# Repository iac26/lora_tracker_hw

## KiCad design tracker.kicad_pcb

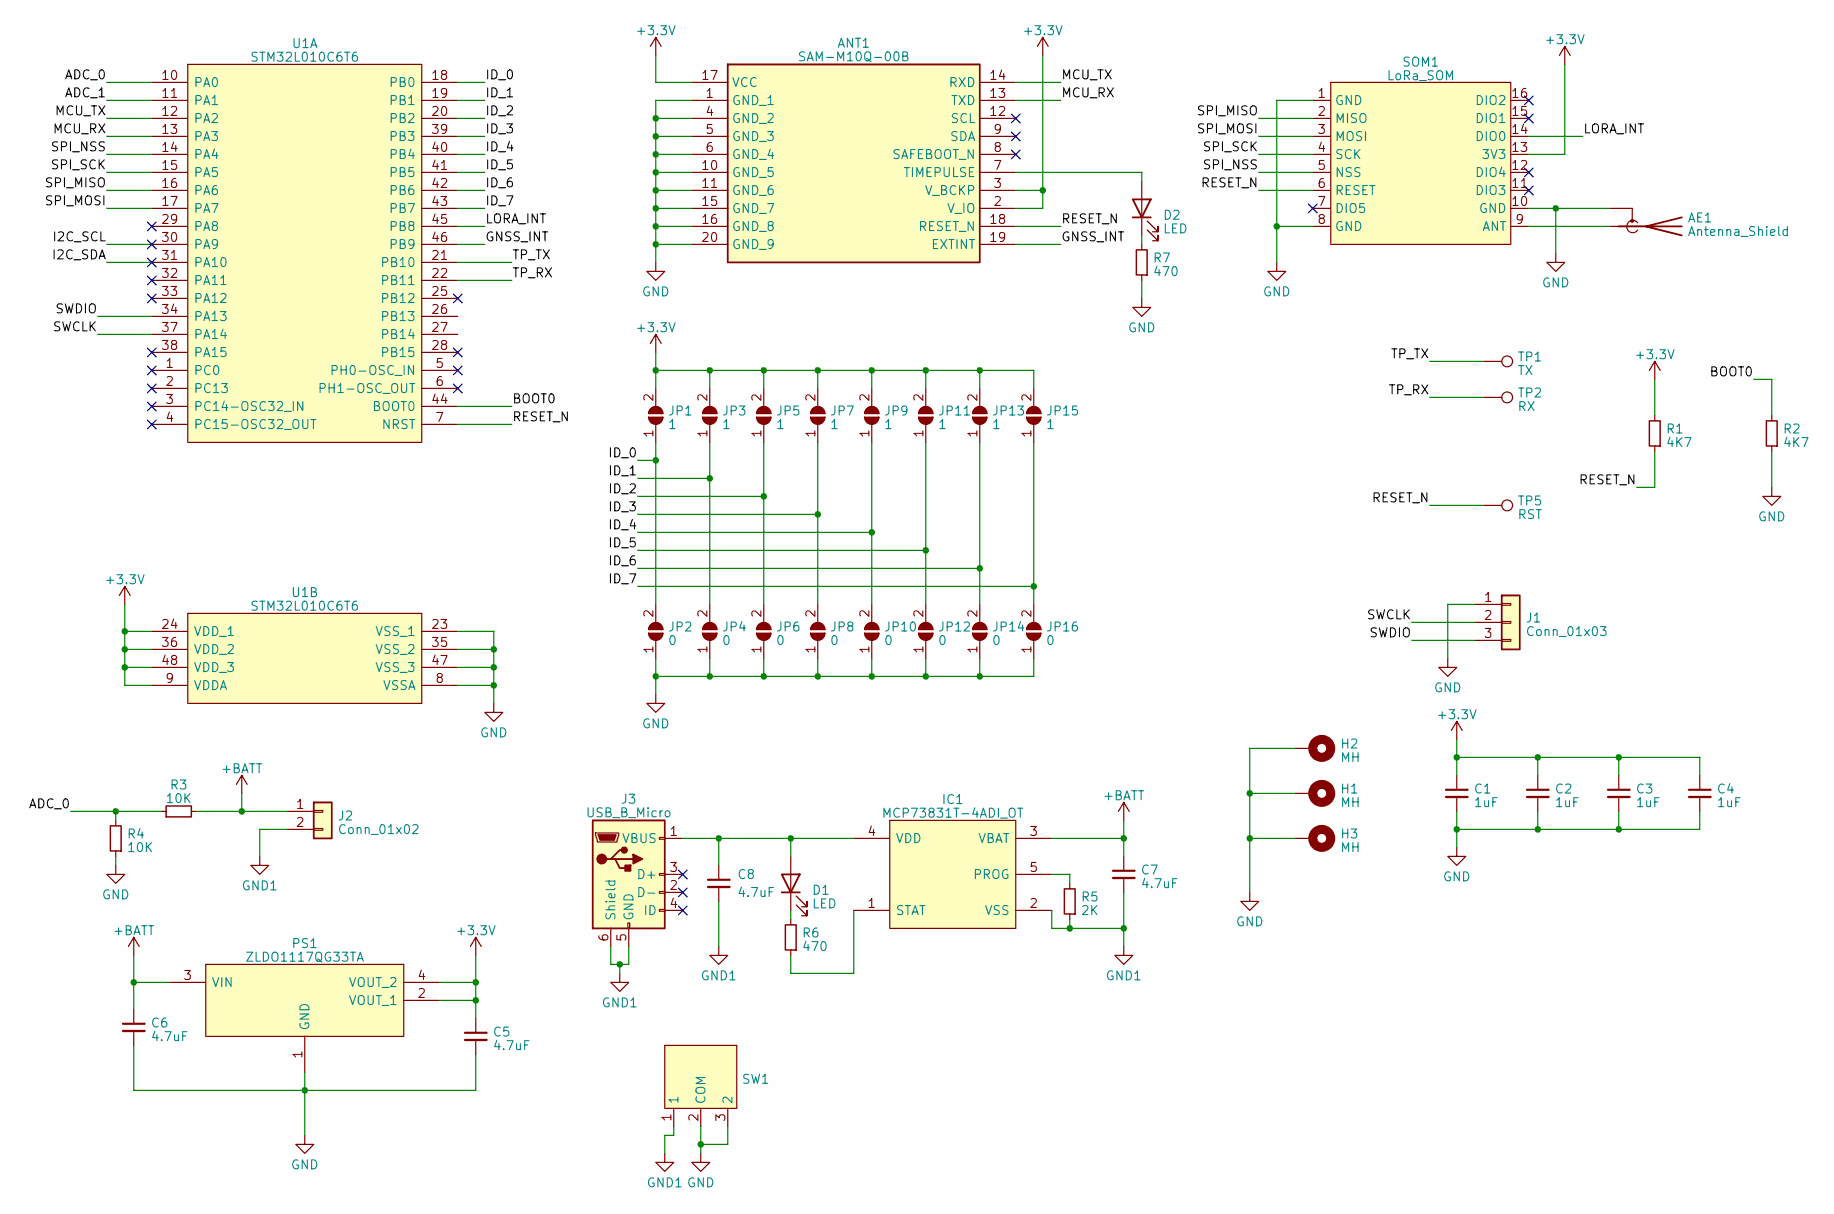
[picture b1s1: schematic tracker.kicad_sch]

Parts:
AE1: Antenna_Shield; SMA_Amphenol_132289_EdgeMount
ANT1: SAM-M10Q-00B; SAMM10Q00B; Manufacturer_Part_Number SAM-M10Q-00B; Mouser Part Number 377-SAM-M10Q-00B
C1, C2, C3, C4: 1uF; C_0603_1608Metric
C5, C6, C7, C8: 4.7uF; C_1206_3216Metric
D1, D2: LED; LED_0603_1608Metric
H1, H2, H3: MH; MountingHole_2.7mm_M2.5_DIN965_Pad_TopBottom
IC1: MCP73831T-4ADI_OT; SOT95P270X145-5N; Manufacturer_Part_Number MCP73831T-4ADI/OT; Mouser Part Number 579-MCP73831T4ADIOT
J1: Conn_01x03; PinHeader_1x03_P2.54mm_Vertical
J2: Conn_01x02; battery_solder
J3: USB_B_Micro; USB_Micro-B_Molex_47346-0001
JP1, JP3, JP5, JP7, JP9, JP11, JP13, JP15: 1; R_0603_1608Metric
JP2, JP4, JP6, JP8, JP10, JP12, JP14, JP16: 0; R_0603_1608Metric
PS1: ZLDO1117QG33TA; SOT230P700X180-4N; Manufacturer_Part_Number ZLDO1117QG33TA; Mouser Part Number 621-ZLDO1117QG33TA
R1, R2: 4K7; R_0603_1608Metric
R3, R4: 10K; R_0603_1608Metric
R5: 2K; R_0603_1608Metric
R6, R7: 470; R_0603_1608Metric
SOM1: LoRa_SOM
SW1: switch
TP1: TX; TestPoint_Pad_D1.0mm
TP2: RX; TestPoint_Pad_D1.0mm
TP5: RST; TestPoint_Pad_D1.0mm
U1: STM32L010C6T6; QFP50P900X900X160-48N; Manufacturer_Part_Number STM32L010C6T6; Mouser Part Number 511-STM32L010C6T6

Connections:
+3.3V: ANT1.2 (V_IO), ANT1.3 (V_BCKP), ANT1.17 (VCC), C1.1, C2.1, C3.1, C4.1, C5.1, JP1.2 (B), JP3.2 (B), JP5.2 (B), JP7.2 (B), JP9.2 (B), JP11.2 (B), JP13.2 (B), JP15.2 (B), PS1.2 (VOUT_1), PS1.4 (VOUT_2), R1.2, SOM1.13 (3V3), U1.9 (VDDA), U1.24 (VDD_1), U1.36 (VDD_2), U1.48 (VDD_3)
+BATT: C6.1, C7.1, IC1.3 (VBAT), J2.1, PS1.3 (VIN), R3.2
/ADC_0: R3.1, R4.2, U1.10 (PA0)
/ADC_1: U1.11 (PA1)
/BOOT0: R2.2, U1.44 (BOOT0)
/GNSS_INT: ANT1.19 (EXTINT), U1.46 (PB9)
/I2C_SCL: U1.30 (PA9)
/I2C_SDA: U1.31 (PA10)
/ID_0: JP1.1 (A), JP2.2 (B), U1.18 (PB0)
/ID_1: JP3.1 (A), JP4.2 (B), U1.19 (PB1)
/ID_2: JP5.1 (A), JP6.2 (B), U1.20 (PB2)
/ID_3: JP7.1 (A), JP8.2 (B), U1.39 (PB3)
/ID_4: JP9.1 (A), JP10.2 (B), U1.40 (PB4)
/ID_5: JP11.1 (A), JP12.2 (B), U1.41 (PB5)
/ID_6: JP13.1 (A), JP14.2 (B), U1.42 (PB6)
/ID_7: JP15.1 (A), JP16.2 (B), U1.43 (PB7)
/LORA_INT: SOM1.14 (DIO0), U1.45 (PB8)
/MCU_RX: ANT1.13 (TXD), U1.13 (PA3)
/MCU_TX: ANT1.14 (RXD), U1.12 (PA2)
/RESET_N: ANT1.18 (RESET_N), R1.1, SOM1.6 (RESET), TP5.1, U1.7 (NRST)
/SPI_MISO: SOM1.2 (MISO), U1.16 (PA6)
/SPI_MOSI: SOM1.3 (MOSI), U1.17 (PA7)
/SPI_NSS: SOM1.5 (NSS), U1.14 (PA4)
/SPI_SCK: SOM1.4 (SCK), U1.15 (PA5)
/SWCLK: J1.2, U1.37 (PA14)
/SWDIO: J1.3, U1.34 (PA13)
/TP_RX: TP2.1, U1.22 (PB11)
/TP_TX: TP1.1, U1.21 (PB10)
GND: AE1.2 (Shield), ANT1.1 (GND_1), ANT1.4 (GND_2), ANT1.5 (GND_3), ANT1.6 (GND_4), ANT1.10 (GND_5), ANT1.11 (GND_6), ANT1.15 (GND_7), ANT1.16 (GND_8), ANT1.20 (GND_9), C1.2, C2.2, C3.2, C4.2, C5.2, C6.2, H1.1, H2.1, H3.1, J1.1, JP2.1 (A), JP4.1 (A), JP6.1 (A), JP8.1 (A), JP10.1 (A), JP12.1 (A), JP14.1 (A), JP16.1 (A), PS1.1 (GND), R2.1, R4.1, R7.1, SOM1.1 (GND), SOM1.8 (GND), SOM1.10 (GND), SW1.2 (COM), SW1.3 (2), U1.8 (VSSA), U1.23 (VSS_1), U1.35 (VSS_2), U1.47 (VSS_3)
GND1: C7.2, C8.2, IC1.2 (VSS), J2.2, J3.5 (GND), J3.6 (Shield), R5.1, SW1.1
unnamed: AE1.1 (A), SOM1.9 (ANT)
unnamed: ANT1.7 (TIMEPULSE), D2.2 (A)
unnamed: C8.1, D1.2 (A), IC1.4 (VDD), J3.1 (VBUS)
unnamed: D1.1 (K), R6.2
unnamed: D2.1 (K), R7.2
unnamed: IC1.5 (PROG), R5.2
unnamed: IC1.1 (STAT), R6.1

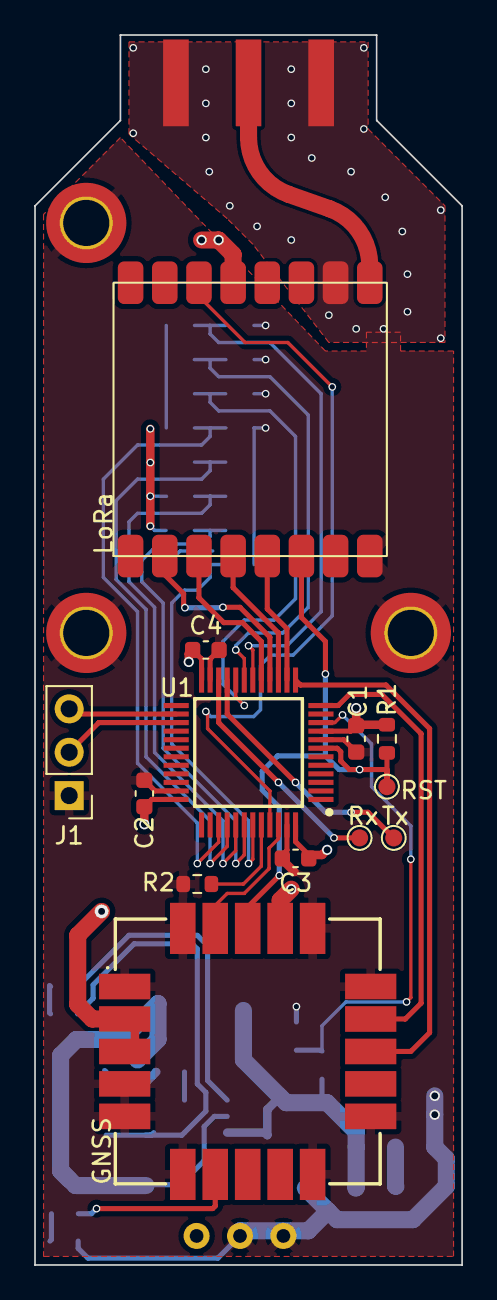
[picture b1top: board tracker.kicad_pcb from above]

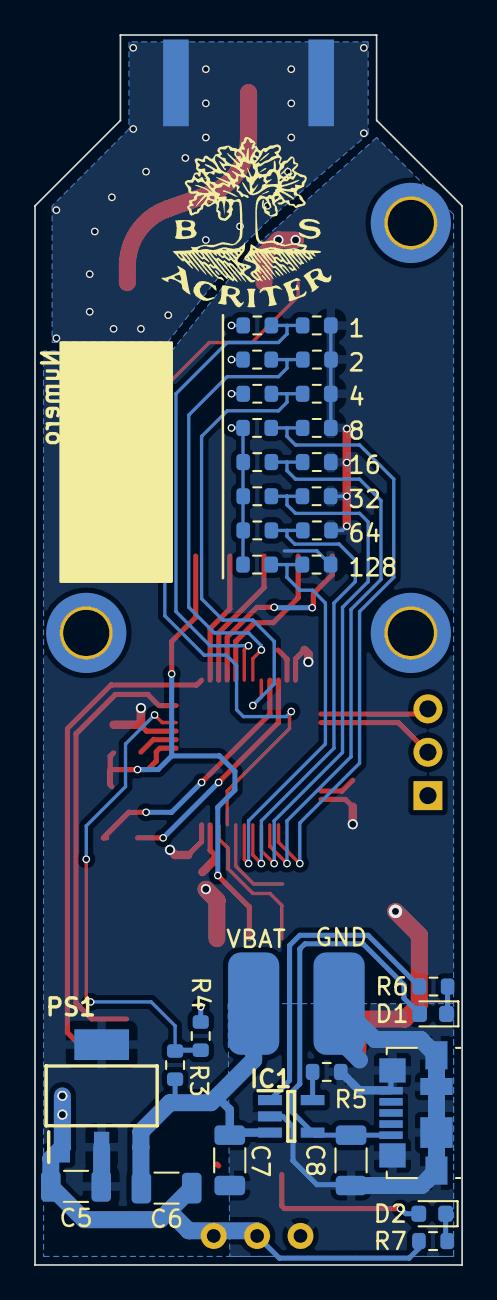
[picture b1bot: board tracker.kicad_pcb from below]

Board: 2 copper layers, 25.0 x 72.0 mm, 49 parts (31 on the bottom side), 34 nets.

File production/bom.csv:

Designator,Footprint,Quantity,Value,LCSC Part #
AE1,SMA_Amphenol_132289_EdgeMount,1,Antenna_Shield,
ANT1,SAMM10Q00B,1,SAM-M10Q-00B,
"C1, C2, C3, C4",0603,4,1uF,
"C5, C6, C7, C8",1206,4,4.7uF,
"D1, D2",0603,2,LED,
"H1, H2, H3",MountingHole_2.7mm_M2.5_DIN965_Pad_TopBottom,3,MH,
IC1,SOT95P270X145-5N,1,MCP73831T-4ADI_OT,
J1,PinHeader_1x03_P2.54mm_Vertical,1,Conn_01x03,
J2,battery_solder,1,Conn_01x02,
J3,USB_Micro-B_Molex_47346-0001,1,USB_B_Micro,
"JP1, JP11, JP13, JP15, JP3, JP5, JP7, JP9",0603,8,1,
"JP10, JP12, JP14, JP16, JP2, JP4, JP6, JP8",0603,8,0,
PS1,SOT230P700X180-4N,1,ZLDO1117QG33TA,
"R1, R2",0603,2,4K7,
"R3, R4",0603,2,10K,
R5,0603,1,2K,
"R6, R7",0603,2,470,
SOM1,LoRa_SOM,1,LoRa_SOM,
SW1,switch,1,~,
TP1,TestPoint_Pad_D1.0mm,1,TX,
TP2,TestPoint_Pad_D1.0mm,1,RX,
TP5,TestPoint_Pad_D1.0mm,1,RST,
U1,QFP50P900X900X160-48N,1,STM32L010C6T6,
